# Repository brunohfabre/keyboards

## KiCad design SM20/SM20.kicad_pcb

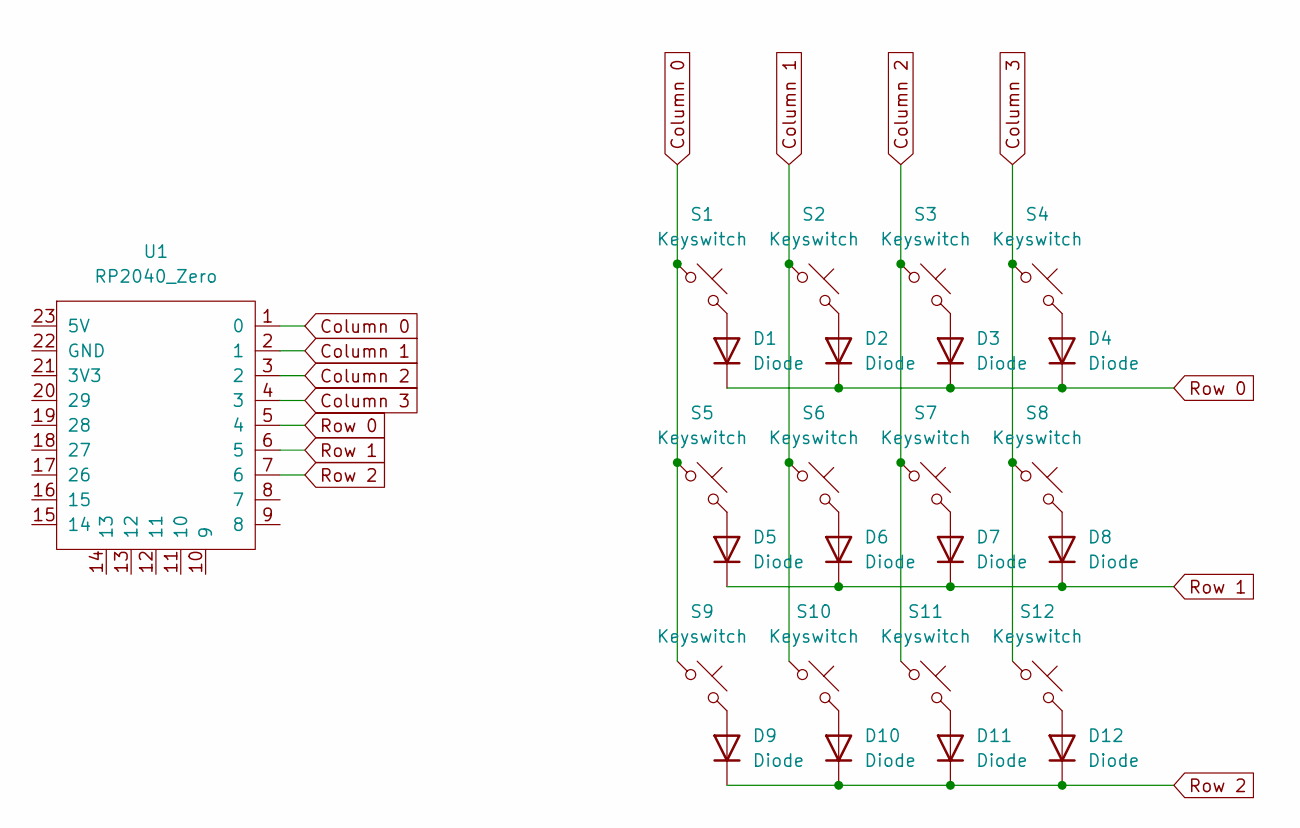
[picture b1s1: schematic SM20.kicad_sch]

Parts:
D1, D2, D3, D4, D5, D6, D7, D8, D9, D10, D11, D12: Diode; Diode_SOD-123
S1, S2, S3, S4, S5, S6, S7, S8, S9, S10, S11, S12: Keyswitch; MX_PCB_1.00u
U1: RP2040_Zero

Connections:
Column 0: S1.1, S5.1, S9.1, U1.1 (0)
Column 1: S2.1, S6.1, S10.1, U1.2 (1)
Column 2: S3.1, S7.1, S11.1, U1.3 (2)
Column 3: S4.1, S8.1, S12.1, U1.4 (3)
unnamed: D1.2 (A), S1.2
unnamed: D2.2 (A), S2.2
unnamed: D3.2 (A), S3.2
unnamed: D4.2 (A), S4.2
unnamed: D5.2 (A), S5.2
unnamed: D6.2 (A), S6.2
unnamed: D7.2 (A), S7.2
unnamed: D8.2 (A), S8.2
unnamed: D9.2 (A), S9.2
unnamed: D10.2 (A), S10.2
unnamed: D11.2 (A), S11.2
unnamed: D12.2 (A), S12.2
Row 0: D1.1 (K), D2.1 (K), D3.1 (K), D4.1 (K), U1.5 (4)
Row 1: D5.1 (K), D6.1 (K), D7.1 (K), D8.1 (K), U1.6 (5)
Row 2: D9.1 (K), D10.1 (K), D11.1 (K), D12.1 (K), U1.7 (6)

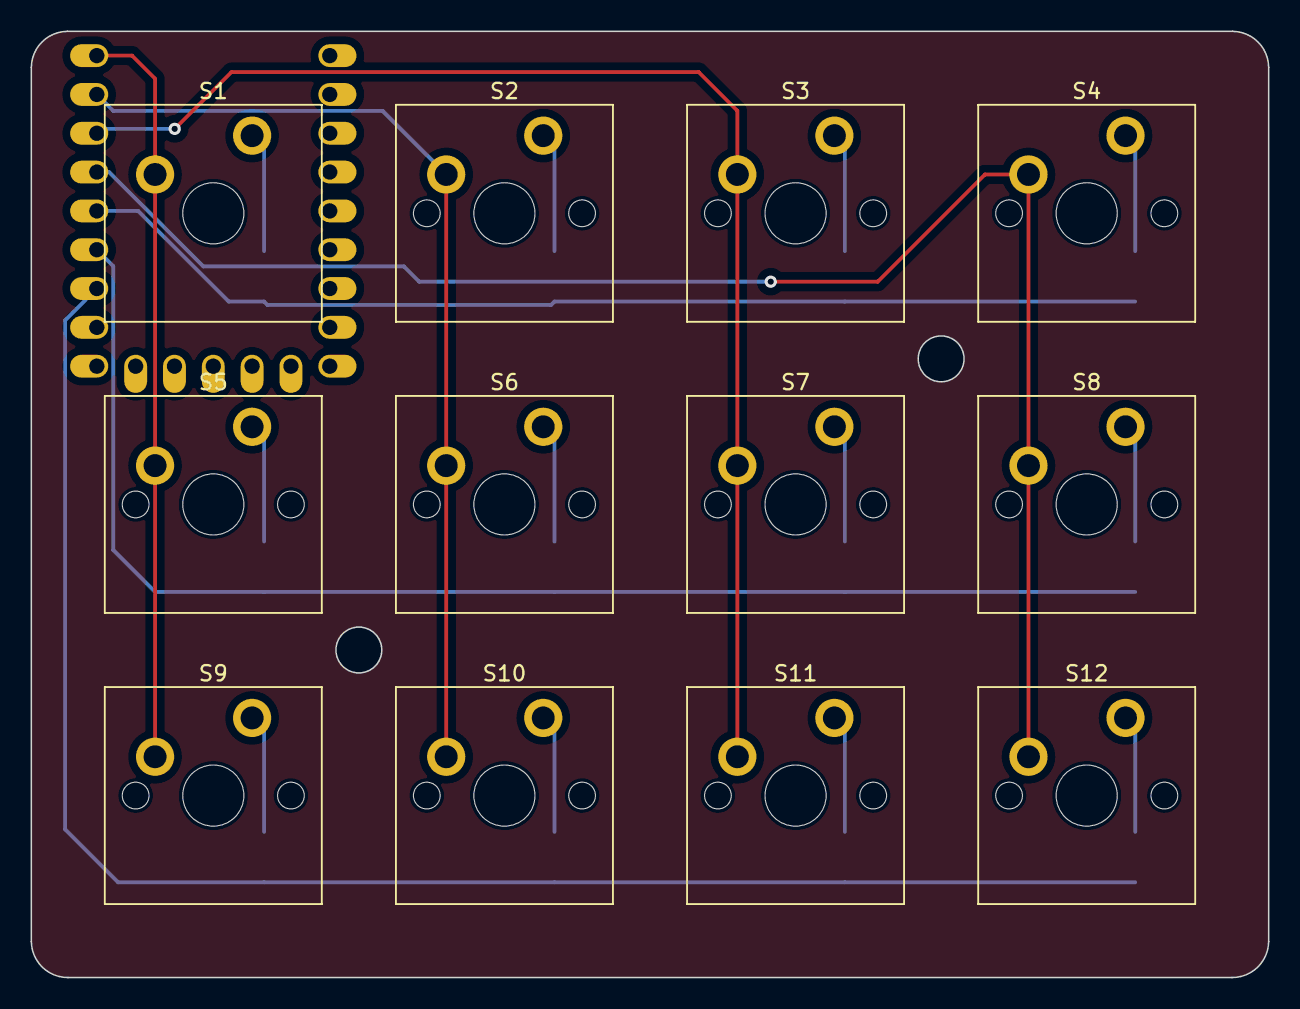
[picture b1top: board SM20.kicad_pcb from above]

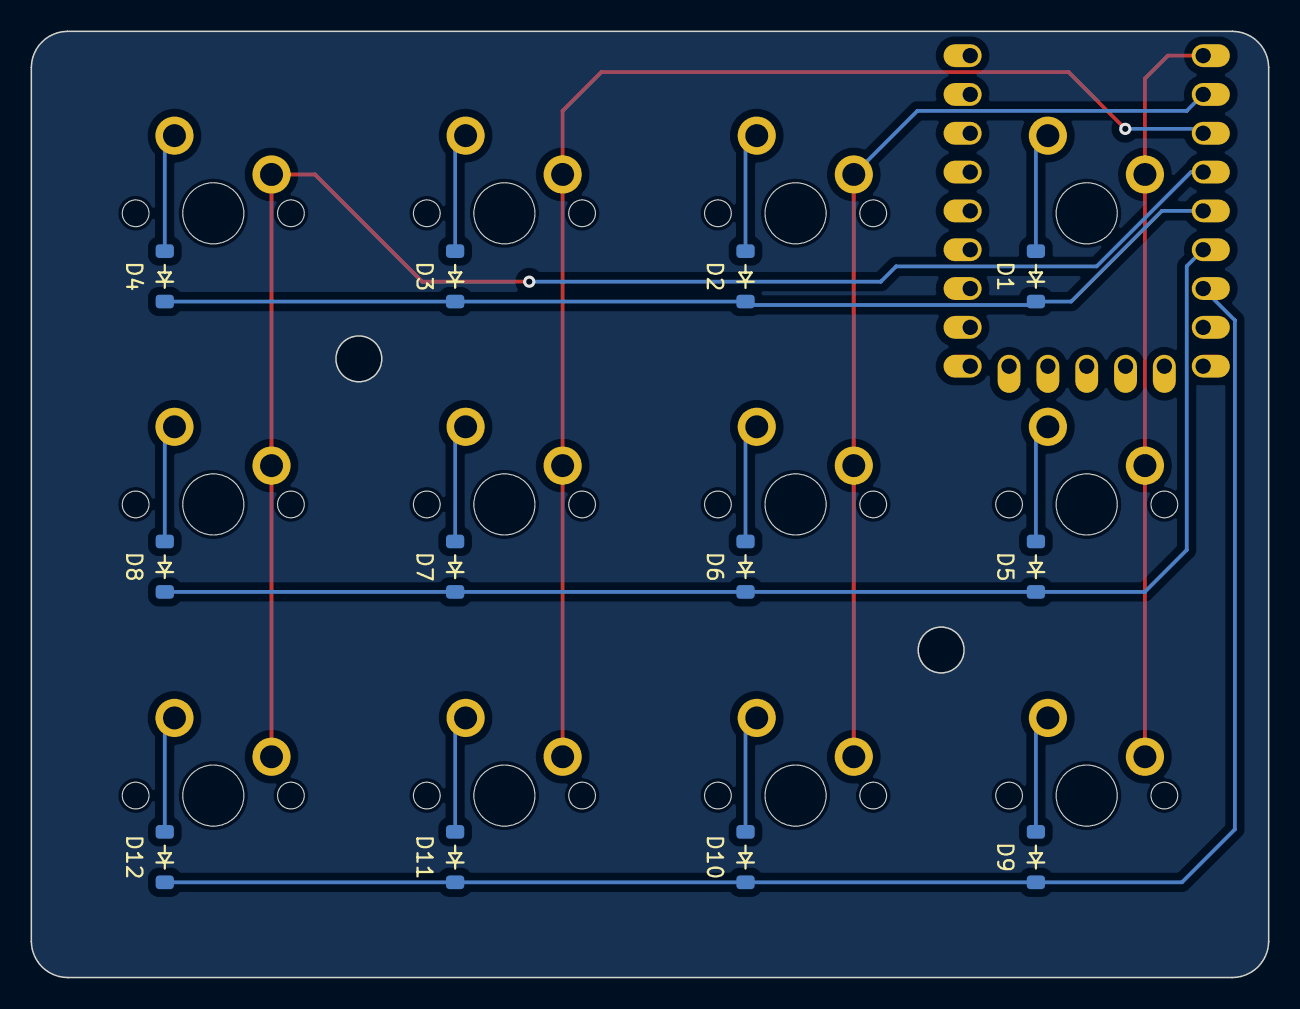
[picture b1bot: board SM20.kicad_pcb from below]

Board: 2 copper layers, 81.0 x 61.9 mm, 25 parts (13 on the bottom side), 19 nets.

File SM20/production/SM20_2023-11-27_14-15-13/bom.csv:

Designator,Footprint,Quantity,Value,LCSC Part #
"D1, D10, D11, D12, D2, D3, D4, D5, D6, D7, D8, D9",Diode_SOD-123,12,Diode,
S1,MX_Plate_1.00u,1,Keyswitch,
"S10, S11, S12, S2, S3, S4, S5, S6, S7, S8, S9",MX_PCB_1.00u,11,Keyswitch,
U1,RP2040_Zero,1,RP2040_Zero,

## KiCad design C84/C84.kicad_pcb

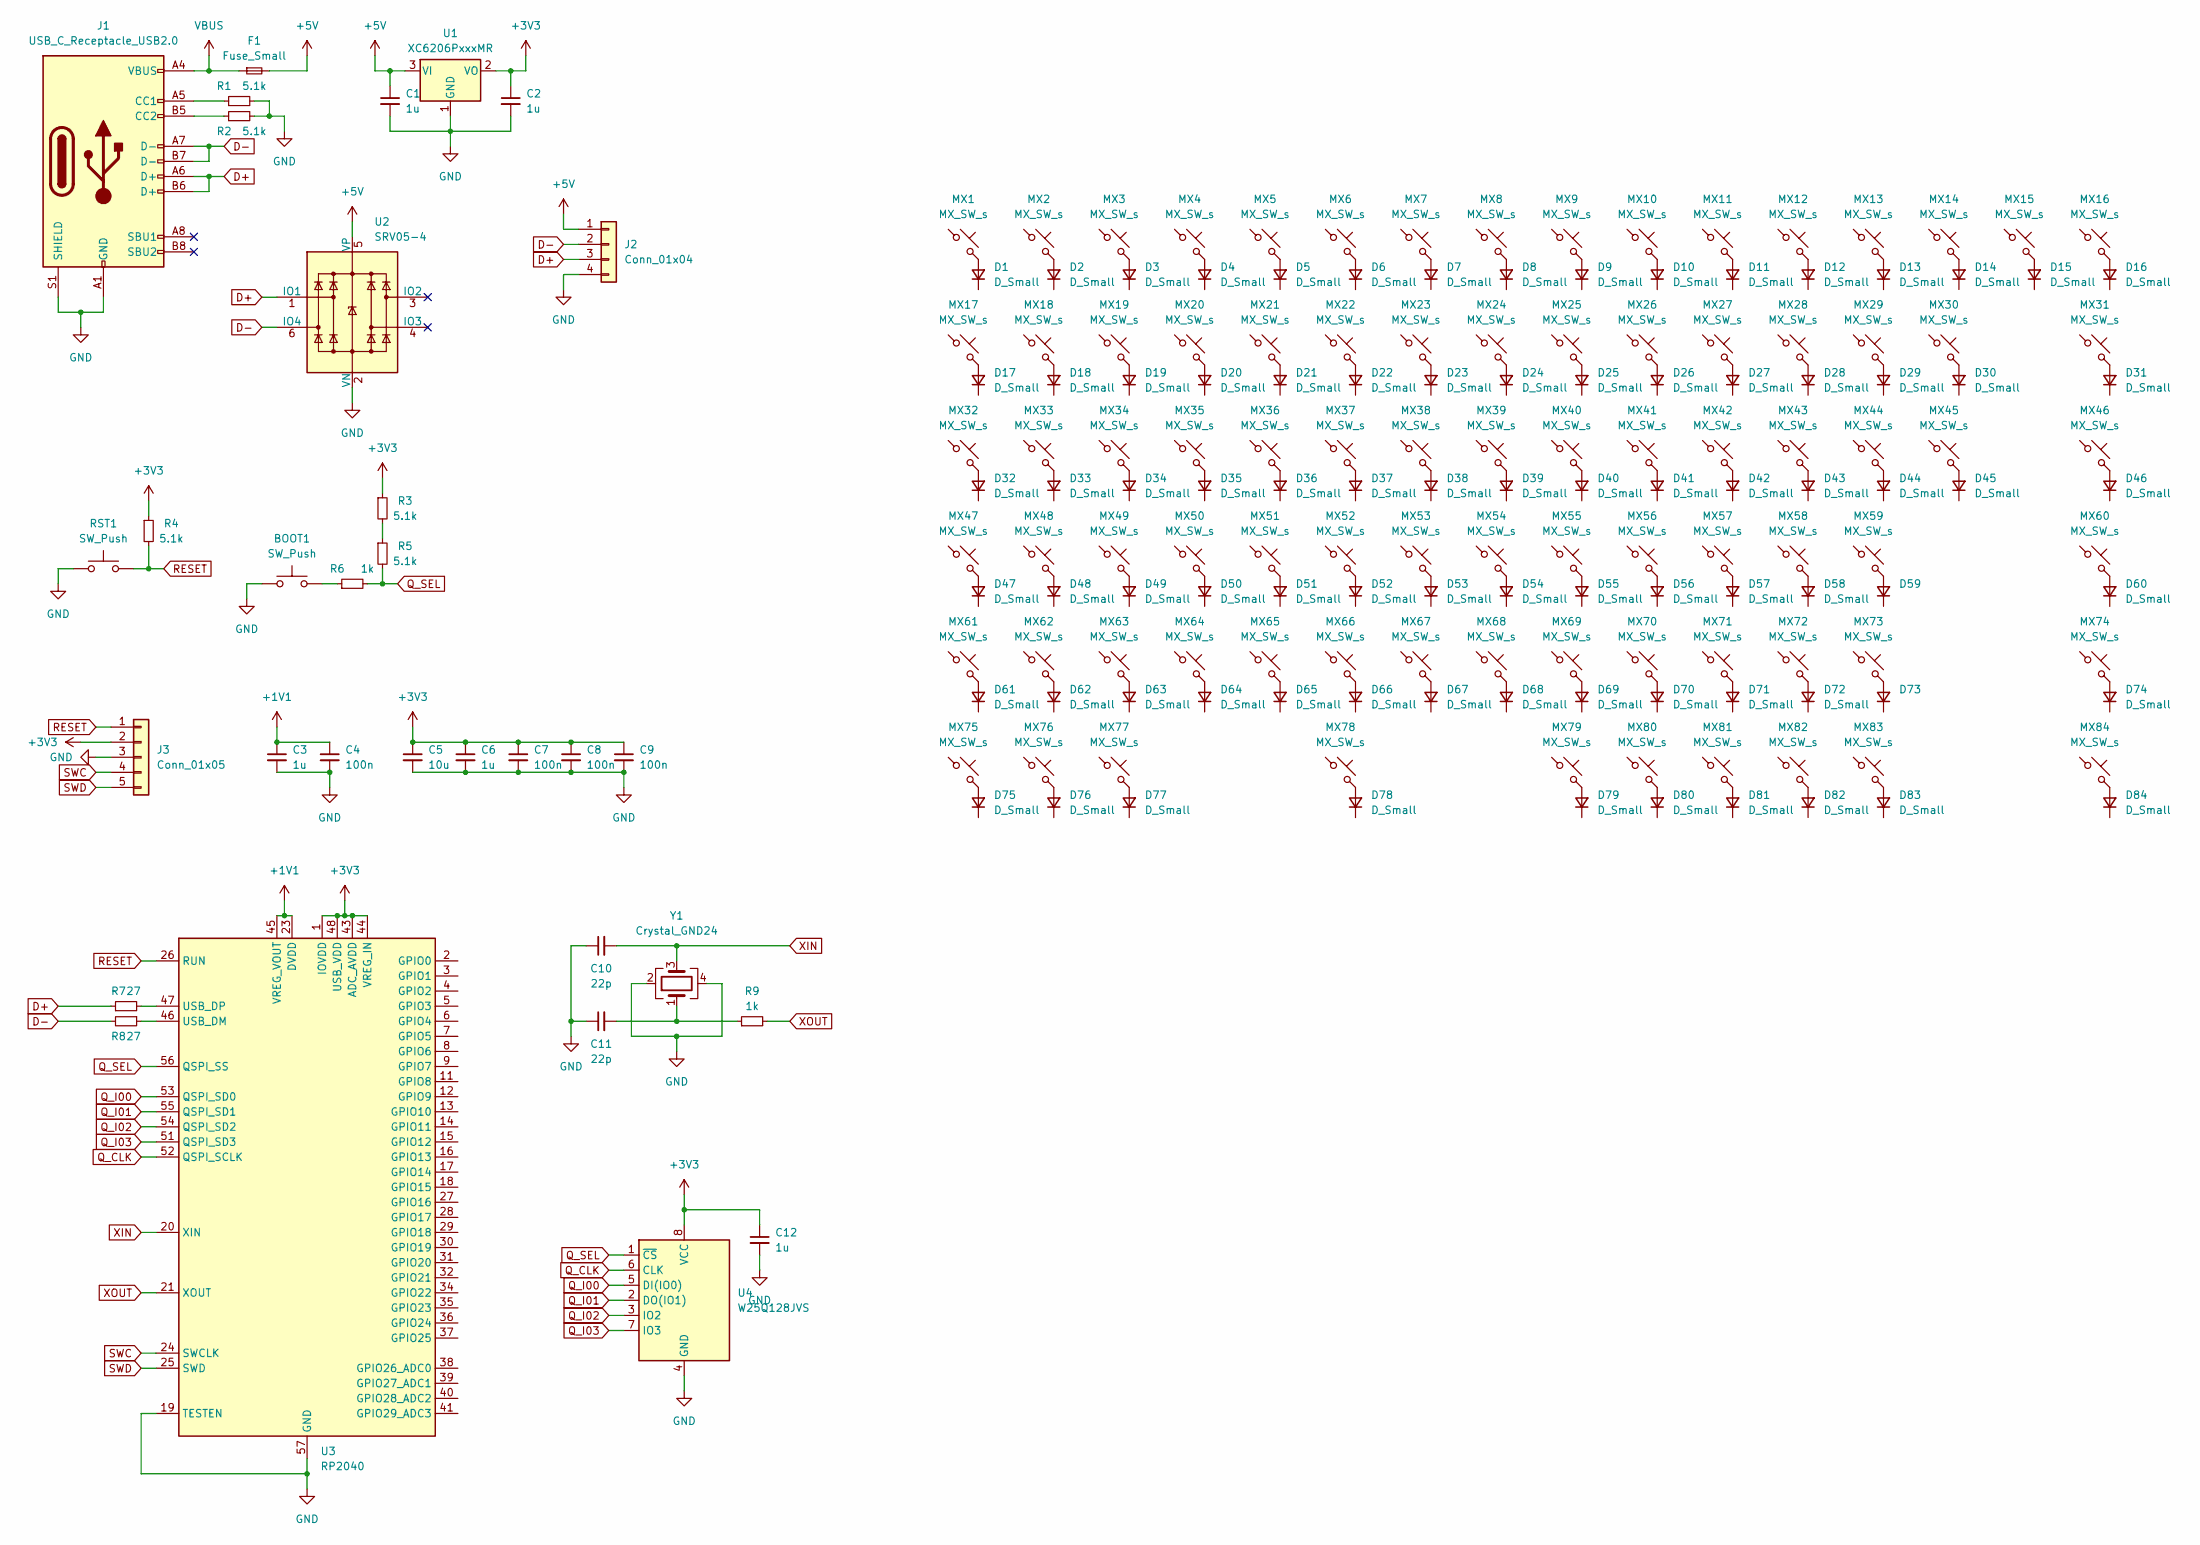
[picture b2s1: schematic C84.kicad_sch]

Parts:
BOOT1: SW_Push; SW_SPST_TL3342
C1, C2, C3, C6, C12: 1u; C_0402_1005Metric
C4, C7, C8, C9: 100n; C_0402_1005Metric
C5: 10u; C_0603_1608Metric
C10, C11: 22p; C_0402_1005Metric
D1, D2, D3, D4, D5, D6, D7, D8, D9, D10, D11, D12, D13, D14, D15, D16, D17, D18, D19, D20, D21, D22, D23, D24, D25, D26, D27, D28, D29, D30, D31, D32, D33, D34, D35, D36, D37, D38, D39, D40, D41, D42, D43, D44, D45, D46, D47, D48, D49, D50, D51, D52, D53, D54, D55, D56, D57, D58, D59, D60, D61, D62, D63, D64, D65, D66, D67, D68, D69, D70, D71, D72, D73, D74, D75, D76, D77, D78, D79, D80, D81, D82, D83, D84: D_Small; D_SOD-123
F1: Fuse_Small; Fuse_1206_3216Metric
J1: USB_C_Receptacle_USB2.0; USB_C_Receptacle_HRO_TYPE-C-31-M-12
J2: Conn_01x04; JST_SH_SM04B-SRSS-TB_1x04-1MP_P1.00mm_Horizontal
J3: Conn_01x05; PinSocket_1x05_P2.54mm_Vertical
MX1, MX2, MX3, MX4, MX5, MX6, MX7, MX8, MX9, MX10, MX11, MX12, MX13, MX14, MX15, MX16, MX17, MX18, MX19, MX20, MX21, MX22, MX23, MX24, MX25, MX26, MX27, MX28, MX29, MX31, MX33, MX34, MX35, MX36, MX37, MX38, MX39, MX40, MX41, MX42, MX43, MX44, MX46, MX48, MX49, MX50, MX51, MX52, MX53, MX54, MX55, MX56, MX57, MX58, MX60, MX62, MX63, MX64, MX65, MX66, MX67, MX68, MX69, MX70, MX71, MX73, MX74, MX79, MX80, MX81, MX82, MX83, MX84: MX_SW_s; SW_MX_1u
MX30: MX_SW_s; STAB_MX_P_2u
MX32, MX45: MX_SW_s; SW_MX_1.5u
MX47, MX72: MX_SW_s; SW_MX_1.75u
MX59, MX61: MX_SW_s; STAB_MX_P_2.25u
MX75, MX76, MX77: MX_SW_s; SW_MX_1.25u
MX78: MX_SW_s; STAB_MX_P_6.25u
R1, R2, R3, R4, R5: 5.1k; R_0402_1005Metric
R6, R9: 1k; R_0402_1005Metric
R7, R8: 27; R_0402_1005Metric
RST1: SW_Push; SW_SPST_TL3342
U1: XC6206PxxxMR; SOT-23-3
U2: SRV05-4; SOT-23-6-routable
U3: RP2040; QFN-56-1EP_7x7mm_P0.4mm_EP3.2x3.2mm
U4: W25Q128JVS; SOIC-8_5.23x5.23mm_P1.27mm
Y1: Crystal_GND24; Crystal_SMD_3225-4Pin_3.2x2.5mm

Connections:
+1V1: C3.1, C4.1, U3.23 (DVDD), U3.45 (VREG_VOUT), U3.50 (DVDD)
+3V3: C2.1, C5.1, C6.1, C7.1, C8.1, C9.1, C12.1, J3.2, R3.1, R4.1, U1.2 (VO), U3.1 (IOVDD), U3.10 (IOVDD), U3.22 (IOVDD), U3.33 (IOVDD), U3.42 (IOVDD), U3.43 (ADC_AVDD), U3.44 (VREG_IN), U3.48 (USB_VDD), U3.49 (IOVDD), U4.8 (VCC)
+5V: C1.1, F1.2, J2.1, U1.3 (VI), U2.5 (VP)
D+: J1.A6 (D+), J1.B6 (D+), J2.3, R7.1, U2.1 (IO1)
D-: J1.A7 (D-), J1.B7 (D-), J2.2, R8.2, U2.6 (IO4)
GND: BOOT1.1, C1.2, C2.2, C3.2, C4.2, C5.2, C6.2, C7.2, C8.2, C9.2, C10.1, C11.1, C12.2, J1.A1 (GND), J1.A12 (GND), J1.B1 (GND), J1.B12 (GND), J1.S1 (SHIELD), J2.4, J3.3, R1.2, R2.2, RST1.1, U1.1 (GND), U2.2 (VN), U3.19 (TESTEN), U3.57 (GND), U4.4 (GND), Y1.2, Y1.4
unnamed: BOOT1.2, R6.1
unnamed: C11.2, R9.1, Y1.1
unnamed: D1.2 (A), MX1.2
unnamed: D2.2 (A), MX2.2
unnamed: D3.2 (A), MX3.2
unnamed: D4.2 (A), MX4.2
unnamed: D5.2 (A), MX5.2
unnamed: D6.2 (A), MX6.2
unnamed: D7.2 (A), MX7.2
unnamed: D8.2 (A), MX8.2
unnamed: D9.2 (A), MX9.2
unnamed: D10.2 (A), MX10.2
unnamed: D11.2 (A), MX11.2
unnamed: D12.2 (A), MX12.2
unnamed: D13.2 (A), MX13.2
unnamed: D14.2 (A), MX14.2
unnamed: D15.2 (A), MX15.2
unnamed: D16.2 (A), MX16.2
unnamed: D17.2 (A), MX17.2
unnamed: D18.2 (A), MX18.2
unnamed: D19.2 (A), MX19.2
unnamed: D20.2 (A), MX20.2
unnamed: D21.2 (A), MX21.2
unnamed: D22.2 (A), MX22.2
unnamed: D23.2 (A), MX23.2
unnamed: D24.2 (A), MX24.2
unnamed: D25.2 (A), MX25.2
unnamed: D26.2 (A), MX26.2
unnamed: D27.2 (A), MX27.2
unnamed: D28.2 (A), MX28.2
unnamed: D29.2 (A), MX29.2
unnamed: D30.2 (A), MX30.2
unnamed: D31.2 (A), MX31.2
unnamed: D32.2 (A), MX32.2
unnamed: D33.2 (A), MX33.2
unnamed: D34.2 (A), MX34.2
unnamed: D35.2 (A), MX35.2
unnamed: D36.2 (A), MX36.2
unnamed: D37.2 (A), MX37.2
unnamed: D38.2 (A), MX38.2
unnamed: D39.2 (A), MX39.2
unnamed: D40.2 (A), MX40.2
unnamed: D41.2 (A), MX41.2
unnamed: D42.2 (A), MX42.2
unnamed: D43.2 (A), MX43.2
unnamed: D44.2 (A), MX44.2
unnamed: D45.2 (A), MX45.2
unnamed: D46.2 (A), MX46.2
unnamed: D47.2 (A), MX47.2
unnamed: D48.2 (A), MX48.2
unnamed: D49.2 (A), MX49.2
unnamed: D50.2 (A), MX50.2
unnamed: D51.2 (A), MX51.2
unnamed: D52.2 (A), MX52.2
unnamed: D53.2 (A), MX53.2
unnamed: D54.2 (A), MX54.2
unnamed: D55.2 (A), MX55.2
unnamed: D56.2 (A), MX56.2
unnamed: D57.2 (A), MX57.2
unnamed: D58.2 (A), MX58.2
unnamed: D59.2 (A), MX59.2
unnamed: D60.2 (A), MX60.2
unnamed: D61.2 (A), MX61.2
unnamed: D62.2 (A), MX62.2
unnamed: D63.2 (A), MX63.2
unnamed: D64.2 (A), MX64.2
unnamed: D65.2 (A), MX65.2
unnamed: D66.2 (A), MX66.2
unnamed: D67.2 (A), MX67.2
unnamed: D68.2 (A), MX68.2
unnamed: D69.2 (A), MX69.2
unnamed: D70.2 (A), MX70.2
unnamed: D71.2 (A), MX71.2
unnamed: D72.2 (A), MX72.2
unnamed: D73.2 (A), MX73.2
unnamed: D74.2 (A), MX74.2
unnamed: D75.2 (A), MX75.2
unnamed: D76.2 (A), MX76.2
unnamed: D77.2 (A), MX77.2
unnamed: D78.2 (A), MX78.2
unnamed: D79.2 (A), MX79.2
unnamed: D80.2 (A), MX80.2
unnamed: D81.2 (A), MX81.2
unnamed: D82.2 (A), MX82.2
unnamed: D83.2 (A), MX83.2
unnamed: D84.2 (A), MX84.2
unnamed: J1.A5 (CC1), R1.1
unnamed: J1.B5 (CC2), R2.1
unnamed: R3.2, R5.1
unnamed: R8.1, U3.46 (USB_DM)
unnamed: R7.2, U3.47 (USB_DP)
Q_CLK: U3.52 (QSPI_SCLK), U4.6 (CLK)
Q_I00: U3.53 (QSPI_SD0), U4.5 (DI(IO0))
Q_I01: U3.55 (QSPI_SD1), U4.2 (DO(IO1))
Q_I02: U3.54 (QSPI_SD2), U4.3 (IO2)
Q_I03: U3.51 (QSPI_SD3), U4.7 (IO3)
Q_SEL: R5.2, R6.2, U3.56 (QSPI_SS), U4.1 (~CS)
RESET: J3.1, R4.2, RST1.2, U3.26 (RUN)
SWC: J3.4, U3.24 (SWCLK)
SWD: J3.5, U3.25 (SWD)
VBUS: F1.1, J1.A4 (VBUS), J1.A9 (VBUS), J1.B4 (VBUS), J1.B9 (VBUS)
XIN: C10.2, U3.20 (XIN), Y1.3
XOUT: R9.2, U3.21 (XOUT)

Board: 2 copper layers, 200 parts (200 on the bottom side), 105 nets, no tracks yet.

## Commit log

2023-11-27 add sm20 keyboard
2023-11-27 add nodes
2023-11-27 finish
